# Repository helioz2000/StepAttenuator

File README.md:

# StepAttenuator
### Step Attenuator for Marconi 2955

To replace the original electro-mechanical Step Attenuator which suffers from wear of electro-mechnical components. 

The board is mechanically compatible with the original Marconi step attenuator 

The MCU is normally in deep sleep mode (no clock) to prevent interference. It only wakes up when the MI2955 issues a command to change the attenuation setting.

The board design allows for the MCU section to be separated from the attenuator to be located in a different housing if desired.

The PE4312DS attenuator pads specifiy insertion loss of 1.3dB. With all pads at 0dB the total loss of the board is expected to be around 5dB. To achieve the 0dB setting of the attenuator a RF relay bypassed all attenuator pads.

[Circuit PDF](Doc/StepAttenuatorCircuit.pdf)

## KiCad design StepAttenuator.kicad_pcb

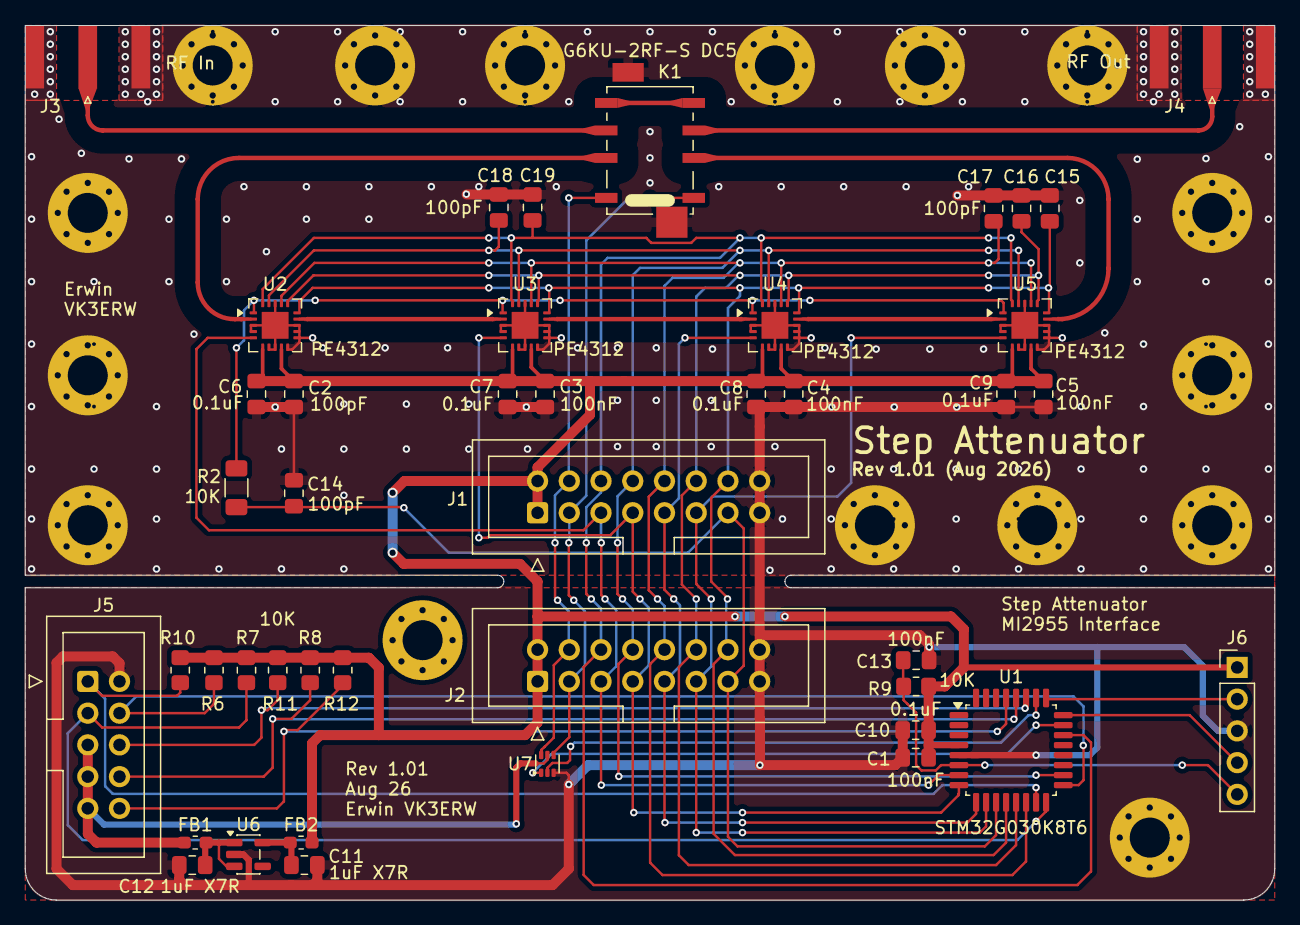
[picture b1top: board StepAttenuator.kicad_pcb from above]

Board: 4 copper layers, 100.0 x 70.0 mm, 59 parts (0 on the bottom side), 37 nets.

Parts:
C1, C3, C4, C5, C13: 100nF; C_0805_2012Metric_Pad1.18x1.45mm_HandSolder
C2, C14, C15, C16, C17, C18, C19: 100pF; C_0805_2012Metric_Pad1.18x1.45mm_HandSolder
C6, C7, C8, C9, C10: 0.1uF; C_0805_2012Metric_Pad1.18x1.45mm_HandSolder
C11, C12: 1uF X7R; C_0805_2012Metric_Pad1.18x1.45mm_HandSolder
FB1, FB2: MH1608A-301Y; L_0603_1608Metric_Pad1.05x0.95mm_HandSolder
J1: IDC-Header_2x08_P2.54mm_Vertical
J2: Conn_02x08_Counter_Clockwise; IDC-Header_2x08_P2.54mm_Vertical
J3: RF In; SMA_Amphenol_132289_EdgeMount
J4: RF Out; SMA_Amphenol_132289_EdgeMount
J5: MI2955; IDC-Header_2x05_P2.54mm_Vertical
J6: Programming; PinHeader_1x05_P2.54mm_Vertical
K1: G6KU-2RF-S DC5; Relay_DPDT_Omron_G6K-2F-RF_special
M3, M3#2, M3#3, M3#4, M3#5, M3#6, M3#7, M3#8, M3#9, M3#10, M3#11, M4, M5, M6, M7, M8: MountingHole_3.2mm_M3_Pad_Via
R2: 10K; R_1206_3216Metric_Pad1.30x1.75mm_HandSolder
R6, R7, R8, R9, R10, R11, R12: 10K; R_0805_2012Metric_Pad1.20x1.40mm_HandSolder
U1: STM32G030K8T6; LQFP-32_7x7mm_P0.8mm
U2, U3, U4, U5: PE4312; QFN-20-1EP_4x4mm_P0.5mm_EP2x2mm
U6: TPS7A2033PDBVR; SOT-23-5
U7: DRV8212DRLR; SOT-563

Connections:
+3.3V: C1.1, C2.1, C3.1, C4.1, C5.1, C6.1, C7.1, C8.1, C9.1, C10.1, FB2.2, J1.1, J1.2, J2.1, J2.2, J6.1, R6.2, R7.2, R8.2, R9.1, R10.2, R11.2, R12.2, U1.4 (VDD), U2.6 (Vdd), U2.9 (Vdd), U3.6 (Vdd), U3.9 (Vdd), U4.6 (Vdd), U4.9 (Vdd), U5.6 (Vdd), U5.9 (Vdd)
+5V: FB1.1, J5.5, J5.7, J5.9, U7.5 (VM)
/Attenuator/RF-1: K1.7, U2.2 (RF1)
/Attenuator/RF-2: U2.14 (RF2), U3.2 (RF1)
/Attenuator/RF-3: U3.14 (RF2), U4.2 (RF1)
/Attenuator/RF-4: U4.14 (RF2), U5.2 (RF1)
/Attenuator/RF-5: K1.2, U5.14 (RF2)
/Attenuator/RF-BYPASS: K1.4, K1.5
/Attenuator/RF-In: J3.1 (In), K1.6
/Attenuator/RF-Out: J4.1 (In), K1.3
/Micro/20dB In: J5.4, R6.1, U1.17 (PB2)
/Micro/20dB Out: J5.6, R11.1, U1.27 (PB3)
/Micro/40dB In a: J5.1, R10.1, U1.15 (PB0)
/Micro/40dB In b: J5.8, R8.1, U1.28 (PB4)
/Micro/40dB Out a: J5.3, R7.1, U1.16 (PB1)
/Micro/40dB Out b: J5.10, R12.1, U1.29 (PB5)
/Micro/NRST: C13.2, J6.5, R9.2, U1.6 (NRST)
/Micro/SWCLK: J6.2, U1.25 (SYS_SWCLK)
/Micro/SWDIO: J6.4, U1.24 (SYS_SWDIO)
C0.5: C19.1, J1.6, J2.6, U1.22 (PA9/PA11), U2.20 (C0.5), U3.20 (C0.5), U4.20 (C0.5), U5.20 (C0.5)
C1: C18.1, J1.8, J2.8, U1.18 (PA8), U2.19 (C1), U3.19 (C1), U4.19 (C1), U5.19 (C1)
C2: C17.1, J1.10, J2.10, U1.14 (PA7), U2.17 (C2), U3.17 (C2), U4.17 (C2), U5.17 (C2)
C4: C16.1, J1.12, J2.12, U1.13 (PA6), U2.16 (C4), U3.16 (C4), U4.16 (C4), U5.16 (C4)
C8: C15.1, J1.14, J2.14, U1.12 (PA5), U2.15 (C8), U3.15 (C8), U4.15 (C8), U5.15 (C8)
C16: C14.1, J1.13, J2.13, R2.2, U1.11 (PA4)
GND: C1.2, C2.2, C3.2, C4.2, C5.2, C6.2, C7.2, C8.2, C9.2, C10.2, C11.2, C12.2, C13.1, C14.2, C15.2, C16.2, C17.2, C18.2, C19.2, J1.15, J1.16, J2.15, J2.16, J3.2 (Ext), J4.2 (Ext), J5.2, J6.3, K1.9, M3.1, M3#2.1, M3#3.1, M3#4.1, M3#5.1, M3#6.1, M3#7.1, M3#8.1, M3#9.1, M3#10.1, M4.1, M5.1, M6.1, M7.1, M8.1, U1.5 (VSS), U2.3 (Data), U2.4 (Clock), U2.7 (PUP1), U2.8 (PUP2), U2.10 (GND), U2.11 (GND), U2.12 (GND), U2.13 (P/S), U2.18 (GND), U2.21, U3.3 (Data), U3.4 (Clock), U3.7 (PUP1), U3.8 (PUP2), U3.10 (GND), U3.11 (GND), U3.12 (GND), U3.13 (P/S), U3.18 (GND), U3.21, U4.3 (Data), U4.4 (Clock), U4.7 (PUP1), U4.8 (PUP2), U4.10 (GND), U4.11 (GND), U4.12 (GND), U4.13 (P/S), U4.18 (GND), U4.21, U5.3 (Data), U5.4 (Clock), U5.7 (PUP1), U5.8 (PUP2), U5.10 (GND), U5.11 (GND), U5.12 (GND), U5.13 (P/S), U5.18 (GND), U5.21, U6.2 (GND), U7.3 (GND)
LE1: J1.5, J2.5, U1.7 (PA0), U2.5 (LE)
LE2: J1.7, J2.7, U1.8 (PA1), U3.5 (LE)
LE3: J1.9, J2.9, U1.9 (PA2), U4.5 (LE)
LE4: J1.11, J2.11, U1.10 (PA3), U5.5 (LE)
unnamed: U1.23 (PA10/PA12), U7.1 (IN1)
unnamed: U1.26 (PA15), U7.2 (IN2)
unnamed: R2.1, U2.1 (C16), U3.1 (C16), U4.1 (C16), U5.1 (C16)
unnamed: C12.1, FB1.2, U6.1 (IN), U6.3 (EN)
unnamed: C11.1, FB2.1, U6.5 (OUT)
RL+: J1.4, J2.4, K1.8, U7.6 (OUT1)
RL-: J1.3, J2.3, K1.1, U7.4 (OUT2)

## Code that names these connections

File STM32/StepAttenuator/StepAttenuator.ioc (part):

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Mcu.Name=STM32G030K(6-8)Tx
Mcu.Package=LQFP32
Mcu.UserName=STM32G030K8Tx
PA0.GPIOParameters=GPIO_Label
PA0.GPIO_Label=LE1
PA0.Signal=GPIO_Output
PA1.GPIOParameters=GPIO_Label
PA1.GPIO_Label=LE2
PA1.Signal=GPIO_Output
PA10.Mode=Asynchronous
PA10.Signal=USART1_RX
PA11\ [PA9].GPIOParameters=GPIO_Label
PA11\ [PA9].GPIO_Label=C05
PA11\ [PA9].Signal=GPIO_Output
PA12\ [PA10].GPIOParameters=GPIO_Label
PA12\ [PA10].GPIO_Label=RLY_OFF
PA12\ [PA10].Signal=GPIO_Output
PA13.Mode=Serial_Wire
PA13.Signal=SYS_SWDIO
PA14-BOOT0.Mode=Serial_Wire
PA14-BOOT0.Signal=SYS_SWCLK
PA15.GPIOParameters=GPIO_Label
PA15.GPIO_Label=RLY_ON
PA15.Signal=GPIO_Output
PA2.GPIOParameters=GPIO_Label
PA2.GPIO_Label=LE3
PA2.Signal=GPIO_Output
PA3.GPIOParameters=GPIO_Label
PA3.GPIO_Label=LE4
PA3.Signal=GPIO_Output
PA4.GPIOParameters=GPIO_Label
PA4.GPIO_Label=C16
PA4.Signal=GPIO_Output
PA5.GPIOParameters=GPIO_Label
PA5.GPIO_Label=C8
PA5.Signal=GPIO_Output
PA6.GPIOParameters=GPIO_Label
PA6.GPIO_Label=C4
PA6.Signal=GPIO_Output
PA7.GPIOParameters=GPIO_Label
PA7.GPIO_Label=C2
PA7.Signal=GPIO_Output
PA8.GPIOParameters=GPIO_Label
PA8.GPIO_Label=C1
PA8.Signal=GPIO_Output
PA9.Mode=Asynchronous
PA9.Signal=USART1_TX
PB0.GPIOParameters=GPIO_PuPd,GPIO_Label,GPIO_ModeDefaultEXTI
PB0.GPIO_Label=ATT40A_IN
PB0.GPIO_ModeDefaultEXTI=GPIO_MODE_IT_FALLING
PB0.GPIO_PuPd=GPIO_PULLUP
PB0.Signal=GPXTI0
PB1.GPIOParameters=GPIO_PuPd,GPIO_Label,GPIO_ModeDefaultEXTI
PB1.GPIO_Label=ATT40A_OUT
PB1.GPIO_ModeDefaultEXTI=GPIO_MODE_IT_FALLING
PB1.GPIO_PuPd=GPIO_PULLUP
PB1.Signal=GPXTI1
PB2.GPIOParameters=GPIO_PuPd,GPIO_Label,GPIO_ModeDefaultEXTI
PB2.GPIO_Label=ATT20_IN
PB2.GPIO_ModeDefaultEXTI=GPIO_MODE_IT_FALLING
PB2.GPIO_PuPd=GPIO_PULLUP
PB2.Signal=GPXTI2
PB3.GPIOParameters=GPIO_PuPd,GPIO_Label,GPIO_ModeDefaultEXTI
PB3.GPIO_Label=ATT20_OUT
PB3.GPIO_ModeDefaultEXTI=GPIO_MODE_IT_FALLING
PB3.GPIO_PuPd=GPIO_PULLUP
PB3.Signal=GPXTI3
PB4.GPIOParameters=GPIO_PuPd,GPIO_Label,GPIO_ModeDefaultEXTI
PB4.GPIO_Label=ATT40B_IN
PB4.GPIO_ModeDefaultEXTI=GPIO_MODE_IT_FALLING
PB4.GPIO_PuPd=GPIO_PULLUP
PB4.Signal=GPXTI4
PB5.GPIOParameters=GPIO_PuPd,GPIO_Label,GPIO_ModeDefaultEXTI
PB5.GPIO_Label=ATT40B_OUT
PB5.GPIO_ModeDefaultEXTI=GPIO_MODE_IT_FALLING
PB5.GPIO_PuPd=GPIO_PULLUP
PB5.Signal=GPXTI5
RCC.HSE_VALUE=8000000
RCC.SYSCLKFreq_VALUE=16000000
board=custom
